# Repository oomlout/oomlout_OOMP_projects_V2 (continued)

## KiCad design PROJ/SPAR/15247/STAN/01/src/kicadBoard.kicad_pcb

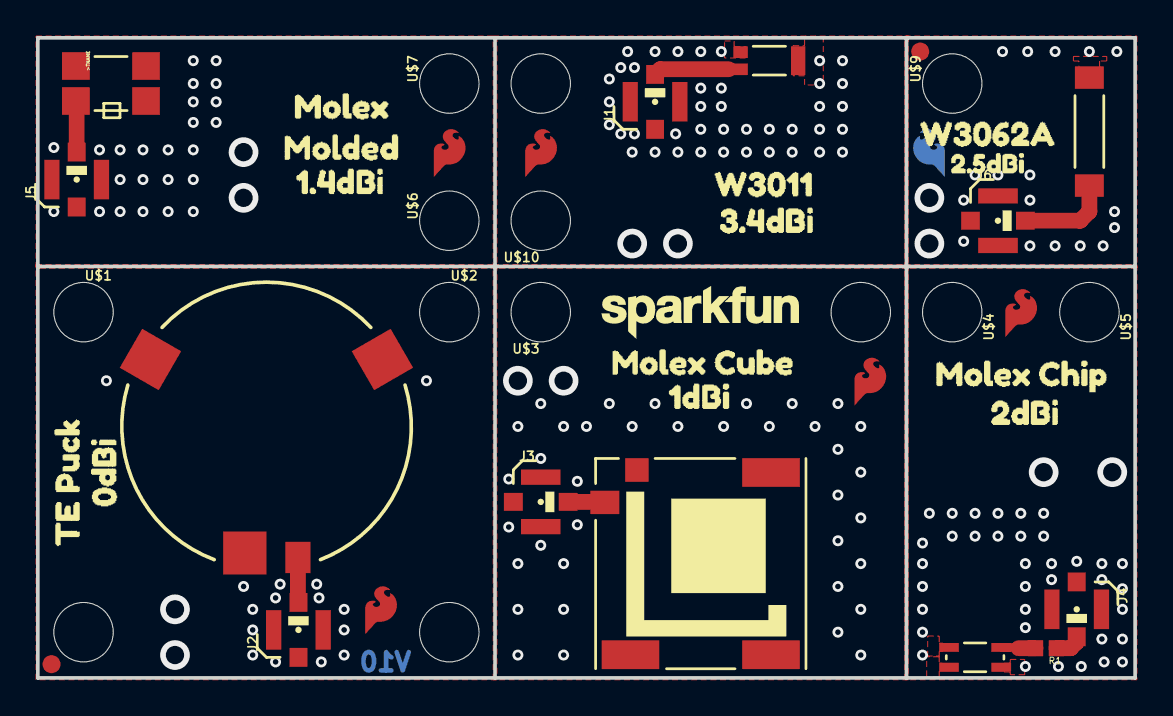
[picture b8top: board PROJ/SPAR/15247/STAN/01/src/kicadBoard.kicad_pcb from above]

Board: 2 copper layers, 61.0 x 35.6 mm, 74 parts (25 on the bottom side), 8 nets.

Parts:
FRAME1: FRAME-LETTER; CREATIVE_COMMONS
J1, J2, J3, J4, J5, J6: U.FL
JP1, JP2, JP5, JP6: STAND-OFF
JP8, JP9: FIDUCIAL1X2; FIDUCIAL-1X2
LOGO1, LOGO2, LOGO3, LOGO4, LOGO5, LOGO6: SFE_LOGO_FLAME.1EXP; SFE_LOGO_FLAME_COPPER_EXPOSED_.1
R1: 0; 0402
U$1, U$2, U$3, U$4, U$5, U$6, U$7, U$9, U$10: STAND-OFF
U$8, U$24, U$25, U$26, U$27, U$28: ANCHOR0
U$11, U$34: 3#4DBI2
U$12, U$42: 0DBI0
U$13, U$57: TE_PUCK7
U$14, U$32: 1#4DBI3
U$15, U$39: 1DBI1
U$16: OSHW-LOGOS; OSHW-LOGO-S
U$17: ORDERING_INSTRUCTIONS
U$18, U$38: 2DBI2
U$19, U$20: MOLEX_CHIP5
U$21, U$22: MOLEX0
U$23: SFE_LOGO_NAME_.1
U$29, U$30: MOLDED1
U$31, U$56: MOLEX_CUBE6
U$33, U$59: W30112
U$35, U$58: W3062A3
U$36: 2#5DBI4
U$37: SFE_LOGO_NAME_FLAME_.1
U$43: ANTENNA10
U$44: 2#5DBI2
U$50: EVALUATION_BOARD15
U$52: GNSS_CHIP13
Y2: PUCK; TE_PUCK
Y3: CUBE; MOLEX_GNSS_CUBE
Y4: CHIP; MOLEX_GNSS_CHIP
Y5: MOLDED; MLOEX_GNSS_MOLDED
Y6: W3062A
Y7: W3011

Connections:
FEED1: J1.FEED, Y7.1
FEED2: J5.FEED, Y5.FEED
FEED3: J2.FEED, Y2.S
FEED4: J3.FEED, Y3.FEED
FEED5: J4.FEED, R1.1
FEED6: J6.FEED, Y6.FEED
GND: J1.1, J1.2, J2.1, J2.2, J3.1, J3.2, J4.1, J4.2, J5.1, J5.2, J6.1, J6.2, Y2.1, Y2.2, Y2.3, Y3.GND, Y4.1, Y4.2, Y4.3, Y6.GND, Y7.2, Y7.3
unnamed: R1.2, Y4.FEED
